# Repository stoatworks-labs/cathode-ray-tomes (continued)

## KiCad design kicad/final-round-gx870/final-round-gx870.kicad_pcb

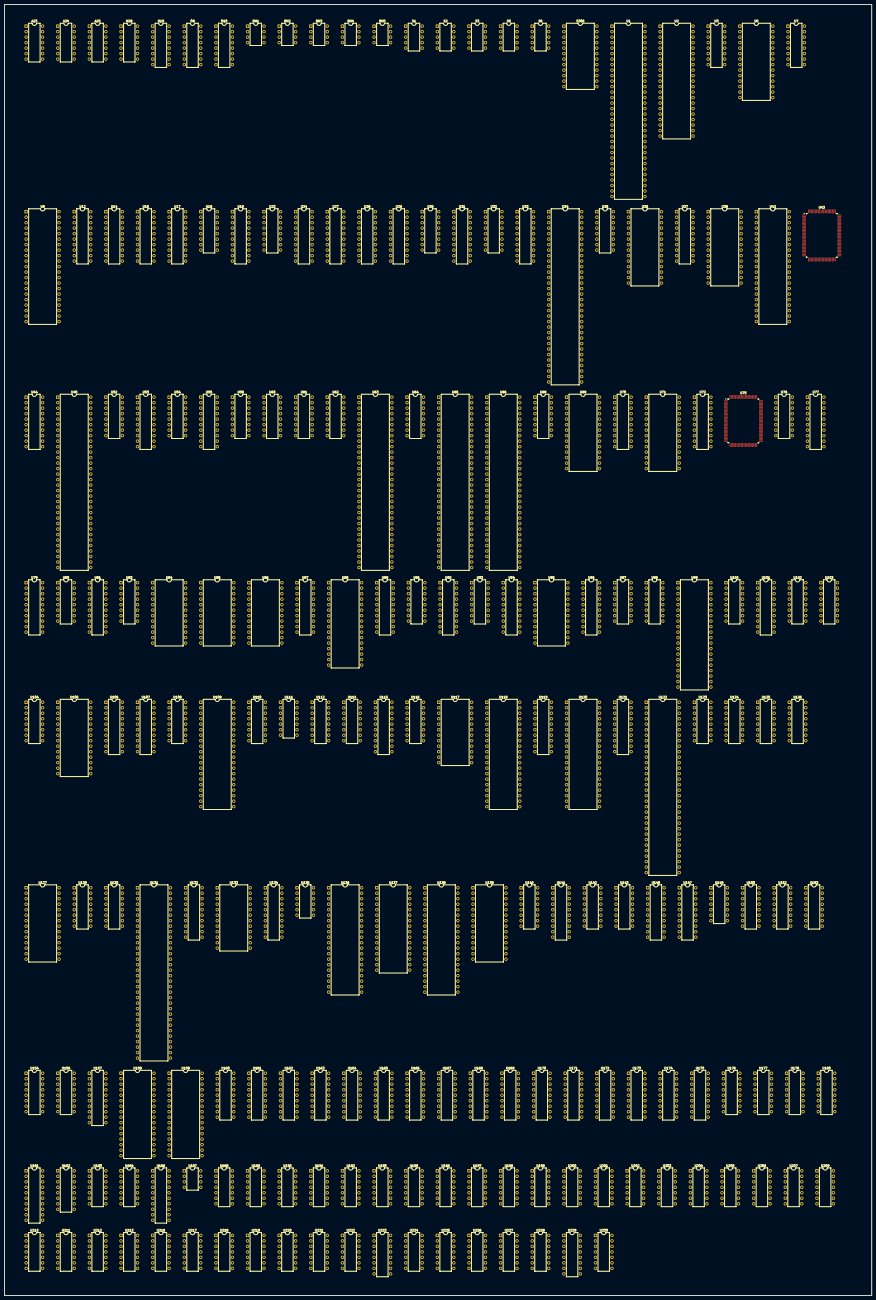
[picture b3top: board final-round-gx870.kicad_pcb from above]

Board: 2 copper layers, 400.8 x 596.7 mm, 205 parts (0 on the bottom side), 1060 nets, no tracks yet.

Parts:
A23, A24, A25: 74LS07; DIP-14_W7.62mm
H28: 74LS04; DIP-14_W7.62mm
N19: 74LS157; DIP-16_W7.62mm
O9, O10: 74LS157; DIP-16_W7.62mm
RN1, RN2, RN3, RN4, RN5: 005273; DIP-8_W7.62mm
S1, S2, S3: 052535; DIP-10_W7.62mm
S5, S6: 007340; DIP-10_W7.62mm
S306: 051550; DIP-24_W15.24mm
U1, U63, U65: 007786; DIP-64_W15.24mm
U2, U42: 007787; DIP-42_W15.24mm
U3, U80, U128, U150: 74LS138; DIP-16_W7.62mm
U5: 27128; DIP-28_W15.24mm
U7, U52, U54, U97, U156, U176, U177: 74LS174; DIP-16_W7.62mm
U8: 007784; DIP-42_W15.24mm
U12, U14, U17, U89, U94, U106, U115, U121, U145, U147, U157: 74LS273; DIP-20_W7.62mm
U15, U28, U53, U55, U79, U81, U87, U92, U101, U132, U134: 74LS374; DIP-20_W7.62mm
U18, U23, U30, U32, U35, U59, U68, U76, U93, U108, U112, U116, U123, U125, U140: 74LS157; DIP-16_W7.62mm
U19, U37, U70, U72, U186: 74LS244; DIP-20_W7.62mm
U24, U27, U29, U31, U33, U44, U77, U96, U107, U119, U141: 74LS245; DIP-20_W7.62mm
U34: 007779; DIP-64_W15.24mm
U36, U38, U69, U71, U105, U139: 6264SL; DIP-28_W15.24mm
U43: 007783; PQFP-100_14x20mm_P0.65mm
U45: 007781; DIP-64_W15.24mm
U60, U61, U62, U64: 74LS153; DIP-16_W7.62mm
U66: 007782; DIP-64_W15.24mm
U75: 007785; PQFP-100_14x20mm_P0.65mm
U83, U91, U98, U100, U102, U104, U110, U114, U152, U153: 74LS257; DIP-16_W7.62mm
U84, U85, U86, U95, U117: HM6116P-3; DIP-24_W15.24mm
U88, U137: 27C010; DIP-32_W15.24mm
U99: Z80CPU; DIP-40_W15.24mm
U103: YM3012; DIP-16_W7.62mm
U109: μPD7759; DIP-40_W15.24mm
U111, U149: 4066; DIP-14_W7.62mm
U118, U120, U136, U138: MX23C4100; DIP-40_W15.24mm
U122: 68000D; DIP-64_W15.24mm
U124, U126, U130, U154: 74LS253; DIP-16_W7.62mm
U127: 27256; DIP-28_W15.24mm
U131: 007232; DIP-64_W15.24mm
U133: YM2151; DIP-24_W15.24mm
U135: MB3731SS; DIP-12_W7.62mm
U142, U143, U182, U229: 74LS367; DIP-16_W7.62mm
U158, U159: 571001D; DIP-32_W15.24mm
U160, U161, U162, U163, U164, U165, U166, U167, U168, U169, U170, U171, U172, U173, U174, U175: 4464; DIP-18_W7.62mm
U178: 74LS399; DIP-16_W7.62mm
U180: 63S141N; DIP-16_W7.62mm
U181: PAL16L8’; DIP-20_W7.62mm
U183, U184: UPC324; DIP-14_W7.62mm
U187: LA6358; DIP-8_W7.62mm
U188, U189, U190, U191, U192, U195, U198, U199, U200, U201, U202, U212, U213, U217, U218, U219, U230: 74LS32; DIP-14_W7.62mm
U193: 74LS86; DIP-14_W7.62mm
U196, U206, U216: 74LS04; DIP-14_W7.62mm
U197, U205: 74LS07; DIP-14_W7.62mm
U203: 74LS20; DIP-14_W7.62mm
U204, U220, U221: 74LS02; DIP-14_W7.62mm
U207, U209, U210, U222, U227: 74LS74; DIP-14_W7.62mm
U211, U225, U226: 74LS08; DIP-14_W7.62mm
U223: 74LS139; DIP-16_W7.62mm
U224: 74LS00; DIP-14_W7.62mm
U228: 74LS21; DIP-14_W7.62mm

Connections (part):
+12V: S306.19, U135.11, U183.4, U184.4
/CPU/A1: O9.5, U3.1, U34.25, U43.16, U83.1, U91.1, U98.1, U100.1, U102.1, U104.1, U107.18, U110.1, U114.1, U124.14, U126.14, U130.14, U152.1, U153.1, U154.14, U201.2, U206.13
/CPU/A2: O9.14, U3.2, U32.3, U34.24, U43.15, U76.2, U93.3, U107.17, U124.2, U126.2, U130.2, U154.2
/CPU/A3: O9.11, U3.3, U32.6, U34.23, U43.14, U76.5, U93.6, U107.16, U150.1
/CPU/A4: N19.2, U32.10, U34.22, U43.13, U76.14, U93.13, U107.15, U150.2
/CPU/A5: N19.5, U32.13, U34.21, U43.12, U76.11, U93.10, U107.14
/CPU/A6: N19.14, U34.20, U43.11, U59.3, U107.13, U108.3, U125.2
/CPU/A7: N19.11, U34.19, U43.10, U59.6, U107.12, U108.6, U125.5
/CPU/A8: O10.2, U34.18, U43.9, U59.10, U107.11, U108.13, U125.14
/CPU/A9: O10.5, U34.17, U43.8, U59.13, U108.10, U125.11, U143.3
/CPU/A10: O10.14, U30.3, U34.15, U43.7, U112.3, U123.2, U143.5
/CPU/A11: O10.11, U30.6, U34.14, U43.6, U112.6, U123.5, U143.7
/CPU/A12: U30.10, U34.13, U43.5, U112.13, U123.14, U143.9
/CPU/A13: U30.13, U43.4, U112.10, U143.11, U211.5
/CPU/A14: U18.3, U140.3, U143.13
/CPU/A15: U18.6, U88.29, U122.43, U137.29, U140.6
/CPU/A16: U18.10, U88.3, U122.44, U137.3, U140.13, U150.4
/CPU/A17: U18.13, U88.2, U122.45, U128.1, U137.2, U140.10, U223.14
/CPU/A18: U23.3, U122.46, U128.2, U223.13
/CPU/A19: U23.6, U122.47, U128.3
/CPU/A20: H28.13, U122.48, U128.4, U191.2
/CPU/CPUCLK: U66.39, U209.3, U209.11, U229.2
/CPU/D0: U8.22, U27.2, U29.9, U33.2, U34.26, U52.3, U54.3, U66.36, U77.9, U83.4, U89.3, U97.3, U98.4, U101.3, U119.2, U124.9, U132.3, U141.18, U142.9, U152.12
/CPU/D1: U8.23, U27.3, U29.8, U33.3, U34.27, U52.4, U54.4, U77.8, U83.7, U89.4, U97.4, U98.7, U101.4, U119.3, U124.7, U132.4, U141.17, U142.7, U152.9
/CPU/D2: U8.24, U27.4, U29.7, U33.4, U34.28, U52.6, U54.6, U77.7, U83.9, U89.7, U98.9, U101.7, U119.4, U132.7, U141.16, U142.5, U152.7, U154.9
/CPU/D3: U8.25, U27.5, U29.6, U33.5, U34.29, U77.6, U83.12, U89.8, U97.6, U98.12, U101.8, U119.5, U132.8, U141.15, U142.3, U152.4, U154.7
/CPU/D4: U8.26, U27.6, U29.5, U33.6, U34.30, U77.5, U89.13, U91.4, U101.13, U102.4, U119.6, U126.9, U132.13, U141.14, U153.12
/CPU/D5: U8.27, U27.7, U29.4, U33.7, U34.31, U77.4, U89.14, U91.7, U97.11, U101.14, U102.7, U119.7, U126.7, U132.14, U141.13, U153.9
/CPU/D6: U8.28, U27.8, U29.3, U33.8, U34.33, U77.3, U89.17, U91.9, U97.13, U101.17, U102.9, U119.8, U130.9, U132.17, U141.12, U153.7
/CPU/D7: U8.29, U27.9, U29.2, U33.9, U34.34, U77.2, U89.18, U91.12, U97.14, U101.18, U102.12, U119.9, U130.7, U132.18, U141.11, U153.4
/CPU/D8: U8.30, U24.9, U31.2, U34.35, U44.2, U96.18, U104.4, U114.4, U134.3
/CPU/D9: U8.31, U24.8, U31.3, U44.3, U96.17, U104.7, U114.7, U134.4
/CPU/D10: U8.33, U24.7, U31.4, U44.4, U96.16, U104.9, U114.9, U134.7
/CPU/D11: U8.34, U24.6, U31.5, U44.5, U96.15, U104.12, U114.12, U134.8
/CPU/D12: U8.35, U24.5, U31.6, U44.6, U96.14, U100.4, U110.4, U134.13
/CPU/D13: U8.36, U24.4, U31.7, U44.7, U96.13, U100.7, U110.7, U134.14
/CPU/D14: U8.37, U24.3, U31.8, U44.8, U96.12, U100.9, U110.9, U134.17
/CPU/D15: U8.38, U24.2, U31.9, U44.9, U96.11, U100.12, U110.12, U134.18
/CPU/DMAINIT: U66.6, U75.77, U181.11, U190.9, U220.8
/CPU/HFLIP: U1.35, U2.16, U42.16, U45.45, U63.35, U66.30, U89.5, U181.5, U193.2, U193.5, U193.10
/CPU/MA1: U88.12, U105.10, U107.2, U122.29, U137.12, U139.10
/CPU/MA2: U88.11, U105.9, U107.3, U122.30, U137.11, U139.9
/CPU/MA3: U88.10, U105.8, U107.4, U122.31, U137.10, U139.8
/CPU/MA4: U88.9, U105.7, U107.5, U122.32, U137.9, U139.7
/CPU/MA5: U88.8, U105.6, U107.6, U122.33, U137.8, U139.6
/CPU/MA6: U88.7, U105.5, U107.7, U122.34, U137.7, U139.5
/CPU/MA7: U88.6, U105.4, U107.8, U122.35, U137.6, U139.4
/CPU/MA8: U88.5, U105.3, U107.9, U122.36, U137.5, U139.3
/CPU/MA9: U88.27, U105.25, U122.37, U137.27, U139.25, U143.2
/CPU/MA10: U88.26, U105.24, U122.38, U137.26, U139.24, U143.4
/CPU/MA11: U88.23, U105.21, U122.39, U137.23, U139.21, U143.6
/CPU/MA12: U88.25, U105.23, U122.40, U137.25, U139.23, U143.10
/CPU/MA13: U88.4, U105.2, U122.41, U137.4, U139.2, U143.12
/CPU/MA14: U88.28, U122.42, U137.28, U143.14
/CPU/MA21: U122.50, U223.2
/CPU/MA22: U122.51, U223.3
/CPU/MA23: U122.52, U191.5, U224.4
/CPU/MD0: U105.11, U122.5, U137.13, U141.2
/CPU/MD1: U105.12, U122.4, U137.14, U141.3
/CPU/MD2: U105.13, U122.3, U137.15, U141.4
/CPU/MD3: U105.15, U122.2, U137.17, U141.5
/CPU/MD4: U105.16, U122.1, U137.18, U141.6
/CPU/MD5: U105.17, U122.64, U137.19, U141.7
/CPU/MD6: U105.18, U122.63, U137.20, U141.8
/CPU/MD7: U105.19, U122.62, U137.21, U141.9
/CPU/MD8: U88.13, U96.2, U122.61, U139.11
/CPU/MD9: U88.14, U96.3, U122.60, U139.12
/CPU/MD10: U88.15, U96.4, U122.59, U139.13
/CPU/MD11: U88.17, U96.5, U122.58, U139.15
/CPU/MD12: U88.18, U96.6, U122.57, U139.16
/CPU/MD13: U88.19, U96.7, U122.56, U139.17
/CPU/MD14: U88.20, U96.8, U122.55, U139.18
/CPU/MD15: U88.21, U96.9, U122.54, U139.19
/CPU/MINT16EN: U97.10, U222.4
/CPU/TIM1: U66.14, U189.10, U206.11
/CPU/VBLANK: U66.58, U222.3
/CPU/VFLIP: U1.36, U63.36, U66.31, U89.2
/CPU/~CPURES: U66.40, U205.3, U205.5
/CPU/~DMACS: U66.61, U188.3
/CPU/~FIXCS: U66.33, U213.5, U213.10, U223.12
/CPU/~FIXDTAC: U66.28, U226.12
/CPU/~MAS: H28.1, H28.3, U122.6, U191.1, U191.4
/CPU/~MDTACK: U122.10, U205.2
/CPU/~MHALT: U122.17, U205.6
/CPU/~MLDS: U122.8, U192.1
/CPU/~MLWR: U43.76, U192.3, U211.1, U213.13, U218.13, U230.2, U230.5
/CPU/~MRESET: U122.18, U205.4
/CPU/~MUDS: U122.7, U192.4
/CPU/~MULWR: U3.4, U34.62, U188.4, U211.3
/CPU/~MUWR: U43.75, U105.27, U139.27, U192.6, U211.2, U213.1, U218.9
/CPU/~OBJCS: U43.77, U189.5, U220.9, U223.10
/CPU/~OBJSCRH: U3.14, U8.39
/CPU/~OBJSCRV: U3.13, U8.40
/CPU/~OCHAROMCS: U98.15, U100.15, U102.15, U104.15, U211.10, U223.7
/CPU/~ROMCS: U88.24, U137.24, U224.1, U226.3
/CPU/~SCVRAMCS: U189.9, U195.5, U204.5, U223.11
/CPU/~SVCHAROMCS: U83.15, U91.15, U110.15, U114.15, U211.9, U223.6
/CPU/~SYSWR: U3.5, U34.61, U128.9, U188.2
/CPU/~V1SCRH: U3.12, U52.9
/CPU/~V2SCRH: U3.10, U54.9
/CPU/~VOROMDTAC: U209.9, U226.13
/CPU/~VRCSET: U128.7, U188.5
/CPU/~WORKCS: U105.20, U128.13, U139.20, U224.2
/CPU/~XCS: U128.5, U189.1, U191.12, U223.4
/Color mixer/1C0: U45.50, U64.5, U192.12
/Color mixer/1C1: U45.49, U64.11, U192.13
/Color mixer/1C2: U45.31, U62.5, U191.9
/Color mixer/1C3: U45.30, U62.11, U191.10
/Color mixer/1C4: U45.29, U60.5
/Color mixer/1C5: U45.2, U60.11
/Color mixer/1C6: U45.1, U61.5
/Color mixer/2C0: U45.57, U64.6, U192.9
/Color mixer/2C1: U45.56, U64.10, U192.10
/Color mixer/2C2: U45.55, U62.6, U212.1
/Color mixer/2C3: U45.54, U62.10, U212.2
/Color mixer/2C4: U45.53, U60.6
/Color mixer/2C5: U45.52, U60.10
/Color mixer/2C6: U45.51, U61.6, U180.2
/Color mixer/CB0: U76.3, U156.12
/Color mixer/CB1: U76.6, U156.15
/Color mixer/CB2: U76.13, U121.2
/Color mixer/CB3: U76.10, U121.5
/Color mixer/CB4: U121.6, U125.3
/Color mixer/CB5: U121.9, U125.6
/Color mixer/CB6: U121.12, U125.13
/Color mixer/CB7: U121.15, U125.10
/Color mixer/CB8: U121.16, U123.3
/Color mixer/CB9: U121.19, U123.6
/Color mixer/CLK2: U7.9, U14.11, U17.11, U34.5, U45.46, U94.11, U115.11, U121.11, U156.9, U178.9, U186.9
/Color mixer/COL0: U64.7, U156.13
/Color mixer/COL1: U64.9, U156.14
/Color mixer/COL2: U62.7, U121.3
/Color mixer/COL3: U62.9, U121.4
/Color mixer/COL4: U60.7, U121.7
/Color mixer/COL5: U60.9, U121.8
/Color mixer/COL6: U61.7, U121.13
/Color mixer/COL7: U61.9, U121.14
/Color mixer/COL8: U121.17, U225.11
/Color mixer/COL9: U121.18, U206.2
/Color mixer/CRTKILL: U18.1, U23.1, U30.1, U32.1, U59.1, U93.1, U97.15, U108.1, U112.1, U140.1, U202.2, U202.4
/Color mixer/FX0: U14.2, U64.3, U230.9
/Color mixer/FX1: U14.5, U64.13, U230.10
/Color mixer/FX2: U14.6, U62.3, U212.13
/Color mixer/FX3: U14.9, U62.13, U212.12
/Color mixer/FX4: U14.12, U60.3
/Color mixer/FX5: U14.15, U60.13
/Color mixer/FX6: U14.16, U61.3
/Color mixer/FX7: U14.19, U61.13
/Color mixer/I0: U77.11, U94.3, U117.17
/Color mixer/I1: U77.12, U94.4, U117.16
/Color mixer/I2: U77.13, U94.7, U117.15
/Color mixer/I3: U77.14, U94.8, U117.14
/Color mixer/I4: U77.15, U94.13, U117.13
/Color mixer/I5: U77.16, U94.14, U117.11
/Color mixer/I6: U77.17, U94.17, U117.10
/Color mixer/I7: U77.18, U94.18, U117.9
/Color mixer/I8: U95.17, U115.3, U119.11
/Color mixer/I9: U95.16, U115.4, U119.12
/Color mixer/I10: U95.15, U115.7, U119.13
/Color mixer/I11: U95.14, U115.8, U119.14
/Color mixer/I12: U95.13, U115.13, U119.15
/Color mixer/I13: U95.11, U115.14, U119.16
/Color mixer/I14: U95.10, U115.17, U119.17
/Color mixer/I15: U95.9, U119.18
/Color mixer/OCD0: U2.21, U64.4, U199.2, U203.5
/Color mixer/OCD1: U2.20, U64.12, U199.1, U203.4
/Color mixer/OCD2: U2.19, U62.4, U200.10, U203.1
/Color mixer/OCD3: U2.18, U62.12, U200.9, U203.2
/Color mixer/OCD4: U42.21, U60.4
/Color mixer/OCD5: U42.20, U60.12
/Color mixer/OCD6: U42.19, U61.4
/Color mixer/OCD7: U42.18, U61.12
/Color mixer/R0: U76.4, U95.2, U117.2
/Color mixer/R1: U76.7, U95.1, U117.1
/Color mixer/R2: U76.12, U95.5, U117.6
/Color mixer/R3: U76.9, U95.6, U117.4
/Color mixer/R4: U95.4, U117.7, U125.4
/Color mixer/R5: U95.7, U117.3, U125.7
/Color mixer/R6: U95.3, U117.8, U125.12
/Color mixer/R7: U95.8, U117.5, U125.9
/Color mixer/R8: U95.23, U117.23, U123.4
/Color mixer/R9: U95.19, U117.19, U123.7
/Color mixer/R10: U95.22, U117.22, U123.12
/Color mixer/SELA: H28.11, U60.14, U61.14, U62.14, U64.14, U202.3
/Color mixer/SELB: U60.2, U61.2, U62.2, U64.2, U202.6, U206.1, U225.13
/Color mixer/SHAD1: A23.9, U156.10, U197.9, U197.11
/Color mixer/SHADOW: U156.6, U180.10
/Color mixer/~CBLK'': A23.11, U115.19, U197.1, U197.3
/Color mixer/~CBLK': U115.18, U156.5
/Color mixer/~CBLK: U66.59, U156.4
/GFX - Fixed layer/1V: U34.1, U66.50, U106.3
/GFX - Fixed layer/2V: U66.51, U106.4
/GFX - Fixed layer/4V: U66.52, U106.7
/GFX - Fixed layer/8H: O9.6, U66.46, U181.4
/GFX - Fixed layer/8V: N19.10, U66.53
/GFX - Fixed layer/16H: O9.13, U66.45
/GFX - Fixed layer/16V: O10.3, U66.54
/GFX - Fixed layer/32H: O9.10, U66.44
/GFX - Fixed layer/32V: O10.6, U66.55
/GFX - Fixed layer/64H: N19.3, U66.43
/GFX - Fixed layer/64V: O10.13, U66.56
/GFX - Fixed layer/128H: N19.6, U66.42
/GFX - Fixed layer/128V: O10.10, U66.57
/GFX - Fixed layer/256H: N19.13, U66.41
/GFX - Fixed layer/FXA0: O9.7, U84.7, U85.7
/GFX - Fixed layer/FXA1: O9.12, U84.5, U85.5
/GFX - Fixed layer/FXA2: O9.9, U84.8, U85.8
/GFX - Fixed layer/FXA3: N19.4, U84.1, U85.1
/GFX - Fixed layer/FXA4: N19.7, U84.23, U85.23
/GFX - Fixed layer/FXA5: N19.12, U84.19, U85.19
/GFX - Fixed layer/FXA6: N19.9, U84.22, U85.22
/GFX - Fixed layer/FXA7: O10.4, U84.4, U85.4
/GFX - Fixed layer/FXA8: O10.7, U84.3, U85.3
/GFX - Fixed layer/FXA9: O10.12, U84.2, U85.2
/GFX - Fixed layer/FXA10: O10.9, U84.6, U85.6
/GFX - Fixed layer/FXD0: U29.11, U85.17, U106.8
/GFX - Fixed layer/FXD1: U29.12, U85.16, U106.13
/GFX - Fixed layer/FXD2: U29.13, U85.15, U106.14
/GFX - Fixed layer/FXD3: U29.14, U85.14, U106.17
/GFX - Fixed layer/FXD4: U29.15, U85.13, U106.18
/GFX - Fixed layer/FXD5: U12.3, U29.16, U85.11
/GFX - Fixed layer/FXD6: U12.4, U29.17, U85.10
/GFX - Fixed layer/FXD7: U12.7, U29.18, U85.9
/GFX - Fixed layer/FXD8: U12.8, U24.11, U84.17
/GFX - Fixed layer/FXD9: U12.13, U24.12, U84.16
/GFX - Fixed layer/FXD10: U12.14, U24.13, U84.15
/GFX - Fixed layer/FXD11: U12.17, U24.14, U84.14
/GFX - Fixed layer/FXD12: U12.18, U24.15, U84.13
/GFX - Fixed layer/FXD13: U24.16, U84.11
/GFX - Fixed layer/FXD14: U24.17, U84.10
/GFX - Fixed layer/FXD15: U24.18, U84.9
/GFX - Fixed layer/FXD[0..15]: U12.11, U106.11, U216.6
/GFX - Fixed layer/P1H: U34.4, U75.46, U181.3, U186.18, U216.13
/GFX - Fixed layer/P2H: N19.1, O9.1, O10.1, U66.17, U79.1, U81.1, U188.9, U188.12, U193.9, U193.12, U199.4, U201.10, U213.4, U216.3, U218.4, U220.3, U220.5
/GFX - Fixed layer/P4H: U66.15, U87.11, U92.11, U188.10, U193.4, U211.4, U211.12, U216.5, U224.10
/GFX - Fixed layer/TIM3: U43.3, U66.11, U213.9
/GFX - Fixed layer/~MREAD2: O9.2, U24.1, U27.1, U29.1, U31.1, U33.1, U43.79, U44.1, U188.1, U188.13, U206.6
/GFX - Fixed layer/~OE: O9.4, U84.20, U85.20
/GFX - Fixed layer/~P1H: U176.9, U177.9, U193.1, U216.12
/GFX - Tiles/1S0: U45.42, U52.2
/GFX - Tiles/1S1: U45.43, U52.5
/GFX - Tiles/1S2: U45.44, U52.7
/GFX - Tiles/1V1: U34.9, U79.3
/GFX - Tiles/1V2: U34.12, U92.3
/GFX - Tiles/2S0: U45.39, U54.2
/GFX - Tiles/2S1: U45.40, U54.5
/GFX - Tiles/2S2: U45.41, U54.7
/GFX - Tiles/2V1: U34.8, U79.4
/GFX - Tiles/2V2: U34.11, U92.4
/GFX - Tiles/4V1: U34.7, U79.7
/GFX - Tiles/4V2: U34.10, U92.7
/GFX - Tiles/B20: U116.2, U132.2, U134.2
/GFX - Tiles/B21: U116.5, U132.5, U134.5
/GFX - Tiles/B22: U116.14, U132.6, U134.6
/GFX - Tiles/B23: U116.11, U132.9, U134.9
/GFX - Tiles/B24: U116.3, U132.12, U134.12
/GFX - Tiles/B25: U116.6, U132.15, U134.15
/GFX - Tiles/B26: U116.13, U132.16, U134.16
/GFX - Tiles/B27: U116.10, U132.19, U134.19
/GFX - Tiles/C0: U45.63, U83.3, U138.13
/GFX - Tiles/C1: U45.62, U83.6, U138.15
/GFX - Tiles/C2: U45.61, U83.10, U138.17
/GFX - Tiles/C3: U45.36, U83.13, U138.19
/GFX - Tiles/C4: U45.35, U91.3, U138.22
/GFX - Tiles/C5: U45.34, U91.6, U138.24
/GFX - Tiles/C6: U45.33, U91.10, U138.26
/GFX - Tiles/C7: U45.28, U91.13, U138.28
/GFX - Tiles/C8: U45.27, U114.3, U138.14
/GFX - Tiles/C9: U45.26, U114.6, U138.16
/GFX - Tiles/C10: U45.25, U114.10, U138.18
/GFX - Tiles/C11: U45.24, U114.13, U138.20
/GFX - Tiles/C12: U45.23, U110.3, U138.23
/GFX - Tiles/C13: U45.22, U110.6, U138.25
/GFX - Tiles/C14: U45.21, U110.10, U138.27
/GFX - Tiles/C15: U45.20, U110.13, U138.29
/GFX - Tiles/C16: U45.19, U83.2, U136.13
/GFX - Tiles/C17: U45.18, U83.5, U136.15
/GFX - Tiles/C18: U45.17, U83.11, U136.17
/GFX - Tiles/C19: U45.15, U83.14, U136.19
/GFX - Tiles/C20: U45.14, U91.2, U136.22
/GFX - Tiles/C21: U45.13, U91.5, U136.24
/GFX - Tiles/C22: U45.12, U91.11, U136.26
/GFX - Tiles/C23: U45.11, U91.14, U136.28
/GFX - Tiles/C24: U45.10, U114.2, U136.14
/GFX - Tiles/C25: U45.9, U114.5, U136.16
/GFX - Tiles/C26: U45.8, U114.11, U136.18
/GFX - Tiles/C27: U45.7, U114.14, U136.20
/GFX - Tiles/C28: U45.6, U110.2, U136.23
/GFX - Tiles/C29: U45.5, U110.5, U136.25
/GFX - Tiles/C30: U45.4, U110.11, U136.27
/GFX - Tiles/C31: U45.3, U110.14, U136.29
/GFX - Tiles/CA0: U93.4, U136.9, U138.9
/GFX - Tiles/CA1: U93.7, U136.8, U138.8
/GFX - Tiles/CA2: U93.12, U136.7, U138.7
/GFX - Tiles/CA3: U93.9, U136.6, U138.6
/GFX - Tiles/CA4: U108.4, U136.5, U138.5
/GFX - Tiles/CA5: U108.7, U136.4, U138.4
/GFX - Tiles/CA6: U108.12, U136.3, U138.3
/GFX - Tiles/CA7: U108.9, U136.2, U138.2
/GFX - Tiles/CA8: U112.4, U136.40, U138.40
/GFX - Tiles/CA9: U112.7, U136.39, U138.39
/GFX - Tiles/CA10: U112.12, U136.38, U138.38
/GFX - Tiles/CA11: U112.9, U136.37, U138.37
/GFX - Tiles/CA12: U136.36, U138.36, U140.4
/GFX - Tiles/CA13: U136.35, U138.35, U140.7
/GFX - Tiles/CA14: U116.4, U136.34, U138.34
/GFX - Tiles/CA15: U116.7, U136.33, U138.33
/GFX - Tiles/CA16: U116.12, U136.32, U138.32
/GFX - Tiles/CA17: U116.9, U136.1, U138.1
/GFX - Tiles/E0: U79.9, U92.9, U93.11
/GFX - Tiles/E1: U79.12, U92.12, U108.2
/GFX - Tiles/E2: U79.15, U92.15, U108.5
/GFX - Tiles/E3: U79.16, U92.16, U108.14
/GFX - Tiles/E4: U79.19, U92.19, U108.11
/GFX - Tiles/E5: U81.2, U87.2, U112.2
/GFX - Tiles/E6: U81.5, U87.5, U112.5
/GFX - Tiles/E7: U81.6, U87.6, U112.14
/GFX - Tiles/E8: U81.9, U87.9, U112.11
/GFX - Tiles/E9: U81.12, U87.12, U140.2
/GFX - Tiles/E10: U81.15, U87.15, U140.5
/GFX - Tiles/E11: U81.16, U87.16, U140.14
/GFX - Tiles/E12: U81.19, U87.19, U140.11
/GFX - Tiles/EV1: U79.2, U92.2, U93.2
/GFX - Tiles/EV2: U79.5, U92.5, U93.5
/GFX - Tiles/EV4: U79.6, U92.6, U93.14
/GFX - Tiles/N2H: U15.11, U28.11, U53.11, U55.11, U87.1, U92.1, U189.13, U216.4, U224.9
/GFX - Tiles/SYNCRLDV: U34.6, U66.25
/GFX - Tiles/V0: U33.18, U38.11, U79.8, U92.8
/GFX - Tiles/V1: U33.17, U38.12, U79.13, U92.13
/GFX - Tiles/V2: U33.16, U38.13, U79.14, U92.14
/GFX - Tiles/V3: U33.15, U38.15, U79.17, U92.17
/GFX - Tiles/V4: U33.14, U38.16, U79.18, U92.18
/GFX - Tiles/V5: U33.13, U38.17, U81.3, U87.3
/GFX - Tiles/V6: U33.12, U38.18, U81.4, U87.4
/GFX - Tiles/V7: U33.11, U38.19, U81.7, U87.7
/GFX - Tiles/V8: U31.18, U36.11, U81.8, U87.8
/GFX - Tiles/V9: U31.17, U36.12, U81.13, U87.13
/GFX - Tiles/V10: U31.16, U36.13, U81.14, U87.14
/GFX - Tiles/V11: U31.15, U36.15, U81.17, U87.17
/GFX - Tiles/V12: U31.14, U36.16, U81.18, U87.18
/GFX - Tiles/V13: U31.13, U36.17, U45.58
/GFX - Tiles/V14: U31.12, U36.18, U45.59
/GFX - Tiles/V15: U31.11, U36.19, U45.60
/GFX - Tiles/VA0: U34.46, U36.10, U38.10
/GFX - Tiles/VA1: U34.47, U36.9, U38.9
/GFX - Tiles/VA2: U34.49, U36.8, U38.8
/GFX - Tiles/VA3: U34.50, U36.7, U38.7
/GFX - Tiles/VA4: U34.51, U36.6, U38.6
/GFX - Tiles/VA5: U34.52, U36.5, U38.5
/GFX - Tiles/VA6: U34.53, U36.4, U38.4
/GFX - Tiles/VA7: U34.54, U36.3, U38.3
/GFX - Tiles/VA8: U34.55, U36.25, U38.25
/GFX - Tiles/VA9: U34.56, U36.24, U38.24
/GFX - Tiles/VA10: U34.57, U36.21, U38.21
/GFX - Tiles/VA11: U34.58, U36.23, U38.23
/GFX - Tiles/VCNTEN: U1.30, U34.2, U63.30, U66.24
/GFX - Tiles/~CLR: U1.29, U2.15, U8.41, U34.63, U42.15, U43.51, U45.47, U63.29, U65.29, U75.24, U186.16
/GFX - Tiles/~HSYNC: U1.34, U34.3, U63.34, U66.27
/GFX - Tiles/~N2HP4H: U189.4, U195.4, U224.8
/GFX - Tiles/~RAMOE: U36.22, U38.22, U211.11
/GFX - Tiles/~RAS: U66.19, U182.4, U182.6, U218.2
/GFX - Tiles/~VRL: U38.27, U218.11
/GFX - Tiles/~VRU: U36.27, U218.8
/IO/BSY: U80.7, U142.15
/IO/BUSY: U109.18, U142.14
/IO/COIN_CNT_1: S306.22, S306.23
/IO/COIN_CNT_2: S306.20, S306.21
/IO/DMAON: U43.2, U97.12, U210.12
/IO/SOUND-ON: U97.7, U227.3
/IO/Y6: RN4.1, U130.12
/IO/Y8: RN4.5, U130.10
/IO/Y10: RN4.7, U126.4
/IO/Y11: RN1.1, U126.5
/IO/Y14: RN1.5, U126.12
/IO/Y15: RN1.7, U126.11
/IO/Y16: RN3.1, U126.10
/IO/Y18: RN3.3, U154.4
/IO/Y19: RN3.5, U154.5
/IO/Y20: RN3.7, U154.6
/IO/Y22: RN5.1, U154.12
/IO/Y23: RN5.3, U154.11
/IO/Y26: RN5.5, U124.4
/IO/Y27: RN5.7, U124.5
/IO/Y28: RN2.1, U124.6
/IO/Y30: RN2.3, U124.12
/IO/Y31: RN2.5, U124.11
/IO/Y32: RN2.7, U124.10
/IO/YN: RN4.3, U130.11
/IO/~AFR: S306.1, U150.13
/IO/~CSYNC: U66.37, U197.13
/IO/~RST: S306.10, U182.14, U186.17
/IO/~SHOOT: U124.1, U124.15, U126.1, U126.15, U130.1, U130.15, U150.11, U154.1, U154.15
/IO/~SOUND-DATA: U101.11, U150.14
/MR~W: U122.9, U150.3, U192.2, U192.5, U206.3, U206.5
/PI0: U89.6, U180.1
/PI1: U89.9, U180.15
/Sound/A0: U109.26, U158.12
/Sound/A1: U109.27, U158.11
/Sound/A2: U109.28, U158.10
/Sound/A3: U109.29, U158.9
/Sound/A4: U109.30, U158.8
/Sound/A5: U109.31, U158.7
/Sound/A6: U109.32, U158.6
/Sound/A7: U109.33, U158.5
/Sound/A8: U109.34, U158.27
/Sound/CK3M58: U133.24, U196.2
/Sound/DA0: U109.35, U147.3, U158.13
/Sound/DA1: U109.36, U147.4, U158.14
/Sound/DA2: U109.37, U147.7, U158.15
/Sound/DA3: U109.38, U147.8
/Sound/DA4: U109.39, U147.13, U158.17
/Sound/DA5: U109.1, U147.14, U158.18
/Sound/DA6: U109.2, U147.17, U158.19
/Sound/DA7: U109.3, U147.18, U158.20
/Sound/RA0: U131.33, U159.24
/Sound/RA1: U131.34, U159.3
/Sound/RA2: U131.36, U159.29
/Sound/RA3: U131.38, U159.28
/Sound/RA4: U131.39, U159.4
/Sound/RA5: U131.41, U159.25
/Sound/RA6: U131.43, U159.23
/Sound/RA7: U131.45, U159.26
/Sound/RA8: U131.44, U159.27
/Sound/RA9: U131.42, U159.5
/Sound/RA10: U131.35, U159.6
/Sound/RA11: U131.40, U159.7
/Sound/RA12: U131.47, U159.8
/Sound/RA13: U131.46, U159.9
/Sound/RA14: U131.49, U159.10
/Sound/RA15: U131.50, U159.11
/Sound/RA16: U131.37, U159.12
/Sound/RD0: U131.25, U159.13
/Sound/RD1: U131.27, U159.14
/Sound/RD2: U131.29, U159.15
/Sound/RD4: U131.30, U159.17
/Sound/RD5: U131.28, U159.18
/Sound/RD6: U131.26, U159.19
/Sound/RD7: U131.24, U159.20
/Sound/SD0: U86.17, U99.14, U101.2, U127.11, U131.1, U133.10, U142.13, U145.3, U157.3, U207.12
/Sound/SD1: U86.16, U99.15, U101.5, U127.12, U131.2, U133.12, U145.4, U157.4, U207.2
/Sound/SD2: U86.15, U99.12, U101.6, U127.13, U131.3, U133.13, U145.7, U157.7
/Sound/SD3: U86.14, U99.8, U101.9, U127.15, U131.4, U133.14, U145.8, U157.8
/Sound/SD4: U86.13, U99.7, U101.12, U127.16, U131.5, U133.15, U145.13, U157.13
/Sound/SD5: U86.11, U99.9, U101.15, U127.17, U131.6, U133.16, U145.14, U157.14
/Sound/SD6: U86.10, U99.10, U101.16, U127.18, U131.7, U133.17, U145.17, U157.17
/Sound/SD7: U86.9, U99.13, U101.19, U127.19, U131.8, U133.18, U145.18, U157.18
/Sound/SDA0: U86.8, U99.30, U127.10, U133.4, U196.9
/Sound/SDA1: U86.19, U99.31, U127.9, U131.59
/Sound/SDA2: U86.2, U99.32, U127.8, U131.60
/Sound/SDA3: U86.22, U99.33, U127.7, U131.61
/Sound/SDA4: U86.23, U99.34, U127.6
/Sound/SDA5: U86.1, U99.35, U127.5
/Sound/SDA6: U86.6, U99.36, U127.4
/Sound/SDA7: U86.7, U99.37, U127.3
/Sound/SDA8: U86.3, U99.38, U127.25
/Sound/SDA9: U86.4, U99.39, U127.24
/Sound/SDA10: U86.5, U99.40, U127.21
/Sound/SDA11: U99.1, U127.23
/Sound/SDA12: U80.1, U99.2, U127.2
/Sound/SDA13: U80.2, U99.3, U127.26
/Sound/SDA14: U80.3, U99.4, U127.27
/Sound/SDA15: U80.6, U99.5
/Sound/SQ0: U145.2, U149.12
/Sound/SQ1: U145.5, U149.6
/Sound/SQ2: U145.6, U149.5
/Sound/SQ3: U145.9, U149.13
/Sound/SQ4: U111.12, U145.12
/Sound/SQ5: U111.6, U145.15
/Sound/SQ6: U111.5, U145.16
/Sound/SQ7: U111.13, U145.19
/Sound/~DACS: U80.12, U131.62
/Sound/~INT: U99.16, U227.6
/Sound/~RFSH: U99.28, U196.5
/Sound/~SDDATAEN: U80.13, U101.1
/Sound/~SDMREQ: U80.5, U99.19
/Sound/~SDRAMCS: U80.15, U86.18
/Sound/~SDRD: U86.20, U99.21, U127.22, U133.6
/Sound/~SDWR: U86.21, U99.22, U133.5
/Sound/~SRES: U80.14, U207.3
/Sound/~VDIN: U80.10, U157.11
/Sound/~VST: U80.9, U207.11
/Sprites1/BEFLAG: U8.4, U43.49, U181.1
/Sprites1/CLK21': U181.13, U181.14
/Sprites1/DMA: U8.3, U43.36, U66.4, U181.2
/Sprites1/E0: U53.3, U98.3, U118.13
/Sprites1/E1: U53.4, U98.6, U118.15
/Sprites1/E2: U53.7, U98.10, U118.17
/Sprites1/E3: U53.8, U98.13, U118.19
/Sprites1/E4: U53.13, U102.3, U118.22
/Sprites1/E5: U53.14, U102.6, U118.24
/Sprites1/E6: U53.17, U102.10, U118.26
/Sprites1/E7: U53.18, U102.13, U118.28
/Sprites1/E8: U15.3, U104.3, U118.14
/Sprites1/E9: U15.4, U104.6, U118.16
/Sprites1/E10: U15.7, U104.10, U118.18
/Sprites1/E11: U15.8, U104.13, U118.20
/Sprites1/E12: U15.13, U100.3, U118.23
/Sprites1/E13: U15.14, U100.6, U118.25
/Sprites1/E14: U15.17, U100.10, U118.27
/Sprites1/E15: U15.18, U100.13, U118.29
/Sprites1/E16: U28.3, U98.2, U120.13
/Sprites1/E17: U28.4, U98.5, U120.15
/Sprites1/E18: U28.7, U98.11, U120.17
/Sprites1/E19: U28.8, U98.14, U120.19
/Sprites1/E20: U28.13, U102.2, U120.22
/Sprites1/E21: U28.14, U102.5, U120.24
/Sprites1/E22: U28.17, U102.11, U120.26
/Sprites1/E23: U28.18, U102.14, U120.28
/Sprites1/E24: U55.3, U104.2, U120.14
/Sprites1/E25: U55.4, U104.5, U120.16
/Sprites1/E26: U55.7, U104.11, U120.18
/Sprites1/E27: U55.8, U104.14, U120.20
/Sprites1/E28: U55.13, U100.2, U120.23
/Sprites1/E29: U55.14, U100.5, U120.25
/Sprites1/E30: U55.17, U100.11, U120.27
/Sprites1/E31: U55.18, U100.14, U120.29
/Sprites1/FBREF: U43.53, U75.76, U186.5
/Sprites1/O0: U32.2, U75.54
/Sprites1/O1: U32.5, U75.55
/Sprites1/O2: U32.11, U75.56
/Sprites1/O3: U32.14, U75.57
/Sprites1/O4: U59.2, U75.58
/Sprites1/O5: U59.5, U75.59
/Sprites1/O6: U59.11, U75.60
/Sprites1/O7: U59.14, U75.61
/Sprites1/O8: U30.2, U75.62
/Sprites1/O9: U30.5, U75.63
/Sprites1/O10: U30.11, U75.66
/Sprites1/O11: U30.14, U75.67
/Sprites1/O12: U18.2, U75.68
/Sprites1/O13: U18.5, U75.69
/Sprites1/O14: U18.11, U75.70
/Sprites1/O15: U18.14, U75.71
/Sprites1/O16: U23.2, U75.72
/Sprites1/O17: U23.5, U75.73
/Sprites1/OA0: U43.60, U69.10, U71.10
/Sprites1/OA1: U43.61, U69.9, U71.9
/Sprites1/OA2: U43.62, U69.8, U71.8
/Sprites1/OA3: U43.65, U69.7, U71.7
/Sprites1/OA4: U43.66, U69.6, U71.6
/Sprites1/OA5: U43.67, U69.5, U71.5
/Sprites1/OA6: U43.68, U69.4, U71.4
/Sprites1/OA7: U43.69, U69.3, U71.3
/Sprites1/OA8: U43.70, U69.25, U71.25
/Sprites1/OA9: U43.71, U69.24, U71.24
/Sprites1/OA10: U43.72, U69.21, U71.21
/Sprites1/OA11: U43.73, U69.23, U71.23
/Sprites1/OA12: U43.74, U69.2, U71.2
/Sprites1/OBJBUFINIT: U8.2, U43.55, U66.5, U181.7, U210.11
/Sprites1/OCHF: U65.35, U75.47, U193.13
/Sprites1/OD0: U8.21, U27.18, U43.37, U71.11, U75.6
/Sprites1/OD1: U8.20, U27.17, U43.38, U71.12, U75.7
/Sprites1/OD2: U8.19, U27.16, U43.39, U71.13, U75.8
/Sprites1/OD3: U8.18, U27.15, U43.40, U71.15, U75.9
/Sprites1/OD4: U8.17, U27.14, U43.41, U71.16, U75.10
/Sprites1/OD5: U8.16, U27.13, U43.42, U71.17, U75.11
/Sprites1/OD6: U8.15, U27.12, U43.44, U71.18, U75.12
/Sprites1/OD7: U8.14, U27.11, U43.45, U71.19, U75.13
/Sprites1/OD8: U8.13, U44.18, U69.11, U75.14
/Sprites1/OD9: U8.12, U44.17, U69.12, U75.15
/Sprites1/OD10: U8.10, U44.16, U69.13, U75.16
/Sprites1/OD11: U8.9, U44.15, U69.15, U75.17
/Sprites1/OD12: U8.8, U44.14, U69.16, U75.18
/Sprites1/OD13: U8.7, U44.13, U69.17, U75.19
/Sprites1/OD14: U8.6, U44.12, U69.18, U75.20
/Sprites1/OD15: U8.5, U44.11, U69.19, U75.21
/Sprites1/OSCNTEN: U43.52, U75.79
/Sprites1/SPA0: U32.4, U118.9, U120.9
/Sprites1/SPA1: U32.7, U118.8, U120.8
/Sprites1/SPA2: U32.9, U118.7, U120.7
/Sprites1/SPA3: U32.12, U118.6, U120.6
/Sprites1/SPA4: U59.4, U118.5, U120.5
/Sprites1/SPA5: U59.7, U118.4, U120.4
/Sprites1/SPA6: U59.9, U118.3, U120.3
/Sprites1/SPA7: U59.12, U118.2, U120.2
/Sprites1/SPA8: U30.4, U118.40, U120.40
/Sprites1/SPA9: U30.7, U118.39, U120.39
/Sprites1/SPA10: U30.9, U118.38, U120.38
/Sprites1/SPA11: U30.12, U118.37, U120.37
/Sprites1/SPA12: U18.4, U118.36, U120.36
/Sprites1/SPA13: U18.7, U118.35, U120.35
/Sprites1/SPA14: U18.9, U118.34, U120.34
/Sprites1/SPA15: U18.12, U118.33, U120.33
/Sprites1/SPA16: U23.4, U118.32, U120.32
/Sprites1/SPA17: U23.7, U118.1, U120.1
/Sprites1/TIM3: U43.84, U66.12
/Sprites1/~DMACLR: U43.57, U66.8
/Sprites1/~DMAONS: U181.6, U210.8
/Sprites1/~LRW: U71.27, U181.15
/Sprites1/~LWR: U43.46, U181.18
/Sprites1/~OBJBUFCLR: U43.54, U66.7
/Sprites1/~OSCANCLR: U43.56, U66.26, U75.78
/Sprites1/~URW: U69.27, U181.16
/Sprites1/~UWR: U43.47, U181.9
/Sprites 2/10W: U35.9, U167.4, U168.4
/Sprites 2/11W: U35.12, U164.4, U169.4
/Sprites 2/12W: U35.7, U160.4, U161.4
/Sprites 2/13W: U35.4, U163.4, U171.4
/Sprites 2/20W: U68.9, U162.4, U166.4
/Sprites 2/21W: U68.12, U165.4, U173.4
/Sprites 2/22W: U68.7, U170.4, U172.4
/Sprites 2/23W: U68.4, U174.4, U175.4
/Sprites 2/C0: U19.2, U19.11, U70.2, U70.11, U75.83
/Sprites 2/C1: U19.4, U19.13, U70.4, U70.13, U75.82
/Sprites 2/C2: U19.6, U19.15, U70.6, U70.15, U75.81
/Sprites 2/C3: U19.8, U19.17, U70.8, U70.17, U75.80
/Sprites 2/CLK21: U1.37, U2.14, U8.42, U42.14, U43.50, U63.37, U75.25, U181.8, U186.12
/Sprites 2/CLK22: U65.37, U186.14
/Sprites 2/CX0: U37.2, U37.11, U72.2, U72.11, U75.5
/Sprites 2/CX1: U37.4, U37.13, U72.4, U72.13, U75.4
/Sprites 2/CX2: U37.6, U37.15, U72.6, U72.15, U75.3
/Sprites 2/CX3: U37.8, U37.17, U72.8, U72.17, U75.2
/Sprites 2/FA0: U1.15, U174.14, U175.14
/Sprites 2/FA1: U1.14, U174.13, U175.13
/Sprites 2/FA2: U1.13, U174.12, U175.12
/Sprites 2/FA3: U1.12, U174.11, U175.11
/Sprites 2/FA4: U1.11, U174.8, U175.8
/Sprites 2/FA5: U1.10, U174.7, U175.7
/Sprites 2/FA6: U1.9, U174.6, U175.6
/Sprites 2/FA7: U1.8, U174.10, U175.10
/Sprites 2/FA20: U63.15, U163.14, U171.14
/Sprites 2/FA21: U63.14, U163.13, U171.13
/Sprites 2/FA22: U63.13, U163.12, U171.12
/Sprites 2/FA23: U63.12, U163.11, U171.11
/Sprites 2/FA24: U63.11, U163.8, U171.8
/Sprites 2/FA25: U63.10, U163.7, U171.7
/Sprites 2/FA26: U63.9, U163.6, U171.6
/Sprites 2/FA27: U63.8, U163.10, U171.10
/Sprites 2/FB0: U1.25, U170.14, U172.14
/Sprites 2/FB1: U1.24, U170.13, U172.13
/Sprites 2/FB2: U1.23, U170.12, U172.12
/Sprites 2/FB3: U1.22, U170.11, U172.11
/Sprites 2/FB4: U1.21, U170.8, U172.8
/Sprites 2/FB5: U1.20, U170.7, U172.7
/Sprites 2/FB6: U1.19, U170.6, U172.6
/Sprites 2/FB7: U1.18, U170.10, U172.10
/Sprites 2/FB20: U63.25, U160.14, U161.14
/Sprites 2/FB21: U63.24, U160.13, U161.13
/Sprites 2/FB22: U63.23, U160.12, U161.12
/Sprites 2/FB23: U63.22, U160.11, U161.11
/Sprites 2/FB24: U63.21, U160.8, U161.8
/Sprites 2/FB25: U63.20, U160.7, U161.7
/Sprites 2/FB26: U63.19, U160.6, U161.6
/Sprites 2/FB27: U63.18, U160.10, U161.10
/Sprites 2/FC0: U1.50, U165.14, U173.14
/Sprites 2/FC1: U1.51, U165.13, U173.13
/Sprites 2/FC2: U1.52, U165.12, U173.12
/Sprites 2/FC3: U1.53, U165.11, U173.11
/Sprites 2/FC4: U1.54, U165.8, U173.8
/Sprites 2/FC5: U1.55, U165.7, U173.7
/Sprites 2/FC6: U1.56, U165.6, U173.6
/Sprites 2/FC7: U1.57, U165.10, U173.10
/Sprites 2/FC20: U63.50, U164.14, U169.14
/Sprites 2/FC21: U63.51, U164.13, U169.13
/Sprites 2/FC22: U63.52, U164.12, U169.12
/Sprites 2/FC23: U63.53, U164.11, U169.11
/Sprites 2/FC24: U63.54, U164.8, U169.8
/Sprites 2/FC25: U63.55, U164.7, U169.7
/Sprites 2/FC26: U63.56, U164.6, U169.6
/Sprites 2/FC27: U63.57, U164.10, U169.10
/Sprites 2/FD0: U1.40, U162.14, U166.14
/Sprites 2/FD1: U1.41, U162.13, U166.13
/Sprites 2/FD2: U1.42, U162.12, U166.12
/Sprites 2/FD3: U1.43, U162.11, U166.11
/Sprites 2/FD4: U1.44, U162.8, U166.8
/Sprites 2/FD5: U1.45, U162.7, U166.7
/Sprites 2/FD6: U1.46, U162.6, U166.6
/Sprites 2/FD7: U1.47, U162.10, U166.10
/Sprites 2/FD20: U63.40, U167.14, U168.14
/Sprites 2/FD21: U63.41, U167.13, U168.13
/Sprites 2/FD22: U63.42, U167.12, U168.12
/Sprites 2/FD23: U63.43, U167.11, U168.11
/Sprites 2/FD24: U63.44, U167.8, U168.8
/Sprites 2/FD25: U63.45, U167.7, U168.7
/Sprites 2/FD26: U63.46, U167.6, U168.6
/Sprites 2/FD27: U63.47, U167.10, U168.10
/Sprites 2/HD2: U1.27, U63.27, U75.28
/Sprites 2/HD3: U1.26, U63.26, U75.29
/Sprites 2/HD4: U1.7, U63.7, U75.30
/Sprites 2/HD5: U1.6, U63.6, U75.31
/Sprites 2/HD6: U1.5, U63.5, U75.32
/Sprites 2/HD7: U1.4, U63.4, U75.33
/Sprites 2/HD8: U1.3, U63.3, U75.34
/Sprites 2/HJ0: U1.1, U63.1, U65.1, U75.26
/Sprites 2/HJ1: U1.2, U63.2, U65.2, U75.27
/Sprites 2/P256VD: U2.17, U35.1, U42.17, U63.33, U65.33, U66.23, U68.1, U75.53, U199.5, U206.9, U220.6, U224.13
/Sprites 2/R0: U2.39, U65.25, U167.2, U199.10
/Sprites 2/R1: U2.40, U65.24, U167.3, U199.9
/Sprites 2/R2: U2.41, U65.23, U167.15, U217.1
/Sprites 2/R3: U2.42, U65.22, U167.17, U217.2
/Sprites 2/R4: U42.39, U70.18, U168.2
/Sprites 2/R5: U42.40, U70.16, U168.3
/Sprites 2/R6: U42.41, U70.14, U168.15
/Sprites 2/R7: U42.42, U70.12, U168.17
/Sprites 2/R8: U2.1, U65.21, U164.2, U198.10
/Sprites 2/R9: U2.2, U65.20, U164.3, U198.9
/Sprites 2/R10: U2.3, U65.19, U164.15, U198.5
/Sprites 2/R11: U2.4, U65.18, U164.17, U198.4
/Sprites 2/R12: U42.1, U70.9, U169.2
/Sprites 2/R13: U42.2, U70.7, U169.3
/Sprites 2/R14: U42.3, U70.5, U169.15
/Sprites 2/R15: U42.4, U70.3, U169.17
/Sprites 2/R16: U2.5, U65.15, U160.2, U202.12
/Sprites 2/R17: U2.6, U65.14, U160.3, U202.13
/Sprites 2/R18: U2.7, U65.13, U160.15, U202.10
/Sprites 2/R19: U2.8, U65.12, U160.17, U202.9
/Sprites 2/R20: U19.18, U42.5, U161.2
/Sprites 2/R21: U19.16, U42.6, U161.3
/Sprites 2/R22: U19.14, U42.7, U161.15
/Sprites 2/R23: U19.12, U42.8, U161.17
/Sprites 2/R24: U2.9, U65.11, U163.2, U199.13
/Sprites 2/R25: U2.10, U65.10, U163.3, U199.12
/Sprites 2/R26: U2.12, U65.9, U163.15, U198.13
/Sprites 2/R27: U2.13, U65.8, U163.17, U198.12
/Sprites 2/R28: U19.9, U42.9, U171.2
/Sprites 2/R29: U19.7, U42.10, U171.3
/Sprites 2/R30: U19.5, U42.12, U171.15
/Sprites 2/R31: U19.3, U42.13, U171.17
/Sprites 2/VD0: U1.63, U63.63, U75.44
/Sprites 2/VD1: U1.62, U63.62, U75.41
/Sprites 2/VD2: U1.61, U63.61, U75.40
/Sprites 2/VD3: U1.60, U63.60, U75.39
/Sprites 2/VD4: U1.59, U63.59, U75.38
/Sprites 2/VD5: U1.58, U63.58, U75.37
/Sprites 2/VD6: U1.39, U63.39, U75.36
/Sprites 2/VD7: U1.38, U63.38, U75.35
/Sprites 2/VPD8: H28.9, U75.45
/Sprites 2/W0: U28.2, U53.2, U65.63
/Sprites 2/W1: U28.5, U53.5, U65.62
/Sprites 2/W2: U28.6, U53.6, U65.61
/Sprites 2/W3: U28.9, U53.9, U65.60
/Sprites 2/W4: U28.12, U53.12, U65.59
/Sprites 2/W5: U28.15, U53.15, U65.58
/Sprites 2/W6: U28.16, U53.16, U65.39
/Sprites 2/W7: U28.19, U53.19, U65.38
/Sprites 2/W8: U15.2, U55.2, U65.27
/Sprites 2/W9: U15.5, U55.5, U65.26
/Sprites 2/W10: U15.6, U55.6, U65.7
/Sprites 2/W11: U15.9, U55.9, U65.6
/Sprites 2/W12: U15.12, U55.12, U65.5
/Sprites 2/W13: U15.15, U55.15, U65.4
/Sprites 2/W14: U15.16, U55.16, U65.3
/Sprites 2/W15: U15.19, U55.19, U65.36
/Sprites 2/WDS10: U201.4, U221.13
/Sprites 2/WDS11: U219.4, U221.10
/Sprites 2/WDS12: U219.12, U221.4
/Sprites 2/WDS13: U219.1, U221.1
/Sprites 2/WDS20: U190.4, U220.13
/Sprites 2/WDS21: U195.9, U204.10
/Sprites 2/WDS22: U195.1, U204.1
/Sprites 2/WDS23: U195.12, U204.13
/Sprites 2/X0: U2.22, U65.40, U166.2, U212.10
/Sprites 2/X1: U2.23, U65.41, U166.3, U212.9
/Sprites 2/X1S: U1.31, U63.31, U66.18
/Sprites 2/X2: U2.24, U65.42, U166.15, U212.5
/Sprites 2/X3: U2.25, U65.43, U166.17, U212.4
/Sprites 2/X4: U37.18, U42.22, U162.2
/Sprites 2/X5: U37.16, U42.23, U162.3
/Sprites 2/X6: U37.14, U42.24, U162.15
/Sprites 2/X7: U37.12, U42.25, U162.17
/Sprites 2/X8: U2.26, U65.44, U165.2, U190.2
/Sprites 2/X9: U2.27, U65.45, U165.3, U190.1
/Sprites 2/X10: U2.28, U65.46, U165.15, U190.12
/Sprites 2/X11: U2.29, U65.47, U165.17, U190.13
/Sprites 2/X12: U37.9, U42.26, U173.2
/Sprites 2/X13: U37.7, U42.27, U173.3
/Sprites 2/X14: U37.5, U42.28, U173.15
/Sprites 2/X15: U37.3, U42.29, U173.17
/Sprites 2/X16: U2.30, U65.50, U172.2, U217.13
/Sprites 2/X17: U2.31, U65.51, U172.3, U217.12
/Sprites 2/X18: U2.33, U65.52, U172.15, U219.9
/Sprites 2/X19: U2.34, U65.53, U172.17, U219.10
/Sprites 2/X20: U42.30, U72.18, U170.2
/Sprites 2/X21: U42.31, U72.16, U170.3
/Sprites 2/X22: U42.33, U72.14, U170.15
/Sprites 2/X23: U42.34, U72.12, U170.17
/Sprites 2/X24: U2.35, U65.54, U174.2, U217.5
/Sprites 2/X25: U2.36, U65.55, U174.3, U217.4
/Sprites 2/X26: U2.37, U65.56, U174.15, U217.9
/Sprites 2/X27: U2.38, U65.57, U174.17, U217.10
/Sprites 2/X28: U42.35, U72.9, U175.2
/Sprites 2/X29: U42.36, U72.7, U175.3
/Sprites 2/X30: U42.37, U72.5, U175.15
/Sprites 2/X31: U42.38, U72.3, U175.17
/Sprites 2/~CS1: U160.16, U161.16, U163.16, U164.16, U167.16, U168.16, U169.16, U171.16, U182.3
/Sprites 2/~CS2: U162.16, U165.16, U166.16, U170.16, U172.16, U173.16, U174.16, U175.16, U182.9
/Sprites 2/~FBWM1: U75.49, U203.9
/Sprites 2/~FBWM2: U75.48, U203.10
/Sprites 2/~OE1: U160.1, U161.1, U163.1, U164.1, U167.1, U168.1, U169.1, U171.1, U199.6
/Sprites 2/~OE2: U162.1, U165.1, U166.1, U170.1, U172.1, U173.1, U174.1, U175.1, U201.8
/Sprites 2/~P256VD: U1.33, U220.2, U224.11
/Sprites 2/~RS1: U160.5, U161.5, U163.5, U164.5, U167.5, U168.5, U169.5, U171.5, U182.5
/Sprites 2/~RS2: U162.5, U165.5, U166.5, U170.5, U172.5, U173.5, U174.5, U175.5, U182.7
/Sprites 2/~WR: H28.5, U66.21, U189.12
/~COLORCS: U76.1, U123.1, U125.1, U128.11, U200.1, U201.1
/~EXRES: U52.1, U54.1, U66.63, U89.1, U97.1, U99.26, U103.7, U131.63, U133.3, U157.1, U182.13, U186.3, U207.1, U207.13, U225.9
/~IOCS: U128.10, U150.5
/~MREAD1: U77.1, U96.1, U119.1, U141.1, U206.4
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
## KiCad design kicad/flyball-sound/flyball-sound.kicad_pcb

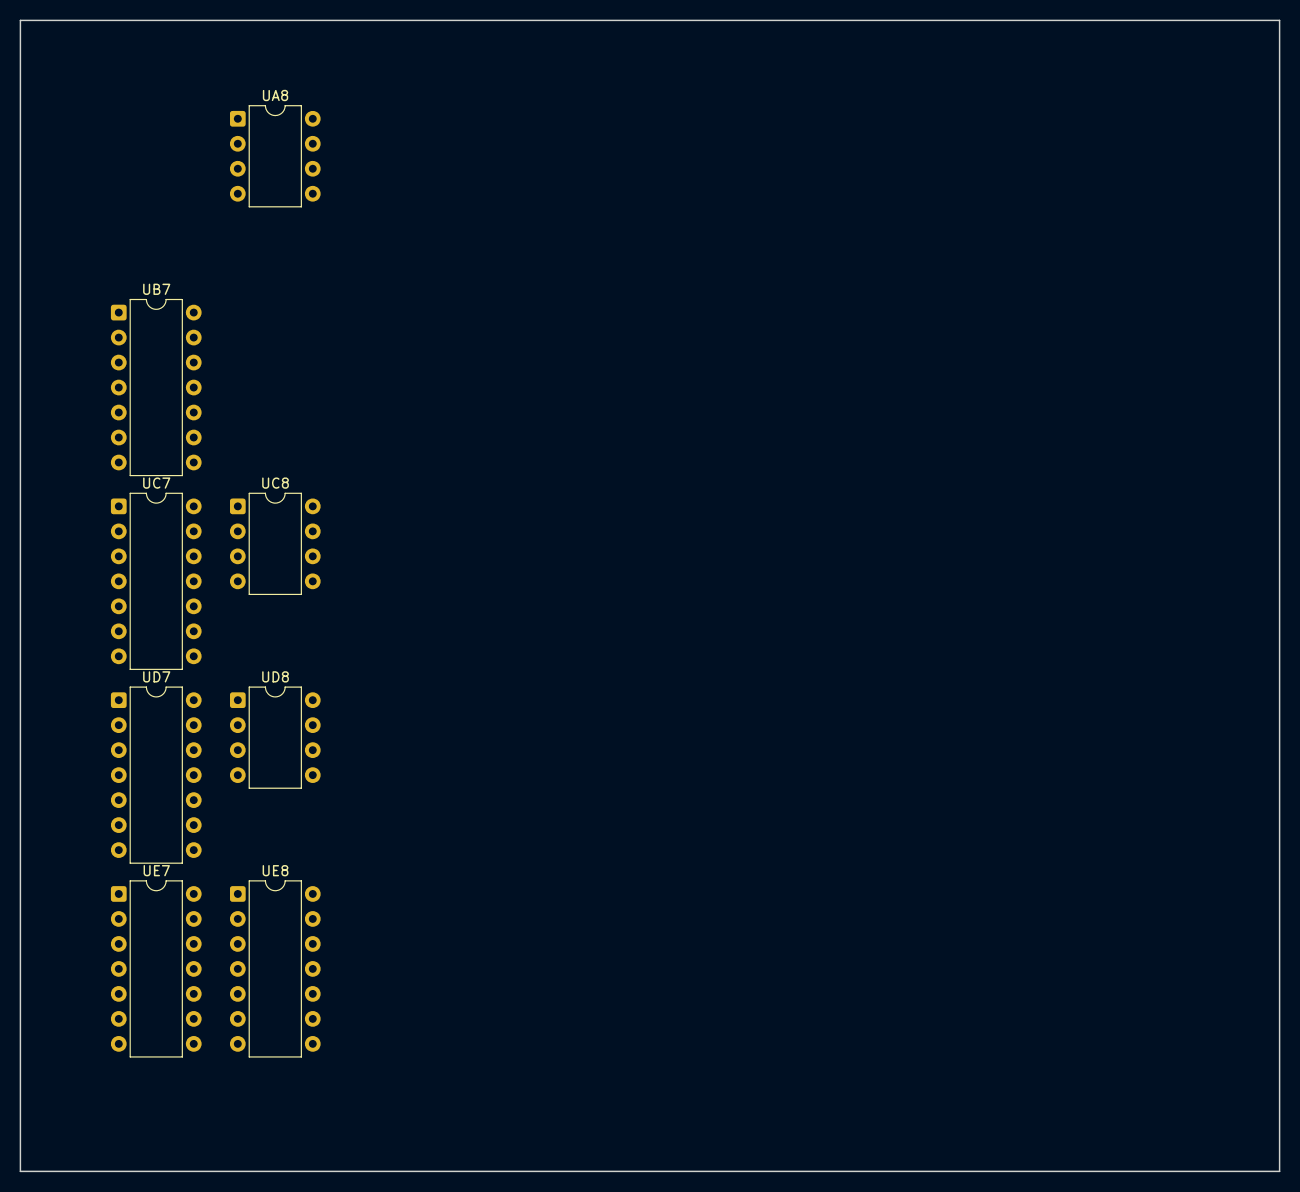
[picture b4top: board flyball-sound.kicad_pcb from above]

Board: 2 copper layers, 128.0 x 117.0 mm, 8 parts (0 on the bottom side), 16 nets, no tracks yet.

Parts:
UA8: MC3340; DIP-8_W7.62mm
UB7: 74164; DIP-14_W7.62mm
UC7: 74164; DIP-14_W7.62mm
UC8: MC3340; DIP-8_W7.62mm
UD7: 7474; DIP-14_W7.62mm
UD8: UA741; DIP-8_W7.62mm
UE7: 7486; DIP-14_W7.62mm
UE8: NE556; DIP-14_W7.62mm

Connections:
+5V: UB7.14, UC7.14, UD7.13, UD7.14, UD8.3, UE7.14, UE8.14
+18V: UA8.8, UC8.8, UD8.7
BAT_SOUND: UE7.1, UE8.4, UE8.10
GND: UA8.3, UB7.7, UC7.7, UC8.3, UD7.2, UD7.7, UD8.4, UE7.4, UE7.5, UE7.7, UE8.7
H256: UB7.8, UC7.8, UD7.4, UD7.11
unnamed: UE8.2, UE8.6
unnamed: UE8.8, UE8.12
unnamed: UE8.3, UE8.11
unnamed: UD7.1, UE7.2, UE7.13
unnamed: UB7.1, UE7.11
unnamed: UB7.5, UE7.10
unnamed: UB7.13, UC7.1
unnamed: UC7.13, UD7.12
unnamed: UD7.9, UE7.9
unnamed: UD7.5, UD7.10
unnamed: UE7.8, UE7.12
